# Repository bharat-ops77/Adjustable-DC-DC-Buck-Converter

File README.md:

# Adjustable CC/CV Buck Converter

An open-source, high-efficiency DC-DC step-down buck converter schematic designed in KiCad. It features **Constant Voltage (CV)** and **Constant Current (CC)** control, making it ideal for battery charging, LED driving, and benchtop power supply projects.

---

## ⚡ Key Features

* **Core IC:** XL4015 Step-Down DC-DC Converter (180 kHz PWM).
* **Control Modes:**
  * **Constant Voltage (CV):** Precision output voltage regulation using `RV2`.
  * **Constant Current (CC):** Adjustable current limit control using `RV1`.
* **Precision Voltage Reference:** Built-in `L78L05` + `TL431` voltage reference circuit for stable current limit thresholds.
* **Low-side Current Sensing:** Precision $0.05\ \Omega$ sense resistor monitored via an `LM358` dual op-amp.
* **Status Indicators:** Integrated onboard LEDs for CC/CV active state indication.
* **Protection:** Screw terminal connectors and input fuse protection.
* **Wattage:**  75W with heatsinks and airflow.
---

## Working Principle

### 1. Main Switching Regulator Stage XL4015 (U2): 
A 180 kHz fixed-frequency step-down PWM DC/DC converter capable of driving up to a 5A load.
  #### ● L1 (40uH) & D1 (Schottky Diode): 
  Standard buck topology output LC filtering network and freewheeling diode.
  #### ● C2, C5, C6: 
  Input and output bulk decoupling capacitors to smooth out ripple voltage.
  ### 2. Voltage Regulation (CV Mode)
  The FB (Feedback, Pin 2) pin of the XL4015 expects a reference voltage (typically around 1.25 V).
  #### ● RV2 (10k) & R4/R5:
  RV2 acts as a feedback potentiometer tied to the output line, allowing you to manually adjust and set the target output voltage.
### 3. Current Control & Sensing Stage (CC Mode)
  #### ● Current Sense Resistor (R6 - 0.05ohm): 
  Connected in series with the low-side return ground, generating a small proportional voltage drop based on load current (Vsense = Iout X   0.05ohm).
  ### 4. Precision Reference (U1, U3, RV1):
   #### ● U1 (L78L05): 
   Standard linear regulator generating a clean 5V rail.
   #### ● U3 (TL431): 
   Precision adjustable reference IC producing a ultra-stable voltage.
   #### ● RV1 (10k Potentiometer): 
   Sets the current limit reference threshold for the operational amplifier.
   ### ● Op-Amp Control (U4 - LM358): 
   #### ● U4A : 
   Compares current sense voltage against current reference set by RV1. When current exceeds the threshold, U4A pulls down the feedback pin via D2, forcing the XL4015 to dial back output duty cycle (Constant Current limiting mode).
   #### ● U4B:
   Drives indicator LEDs (D3 / D4) to visually indicate status (e.g., Constant Voltage mode vs. Constant Current/Charging mode).

 ## ● Here is a well labeled diagram of the circuit schematic:

## ● PCB(First Copper Layer):

## ● PCB(Second Copper Layer):

## ● Rendered 3D Model(Angled View):

## ● Rendered 3D Model(Top View):

## ● Rendered PCB(Front):

## ● Rendered PCB(Back):

### ● Repository Structure

```
├── docs/                   # Datasheet of ICs used
├── manufacturing/          # Gerbers & BOM
│   ├── gerbers/            # Gerber and drill files for PCB fabrication
│   ├── bom/                # Bill of Materials (.csv )
├── Adjustable_Buck.kicad_pcb  # KiCad PCB Layout file
├── Adjustable_Buck.kicad_sch  # KiCad Schematic file
├── Adjustable_Buck.kicad_pro  # KiCad Project file
└── README.md               # This file
 #Adjustable CC/CV buck converter
```

### ● Authored by:

#### ---------------------------------------------------------Bharat Sati-------------------------------------------------------------

### ● License:

#### This project is open-source. Feel free to modify, distribute, and use it for your own applications under the GNU License.

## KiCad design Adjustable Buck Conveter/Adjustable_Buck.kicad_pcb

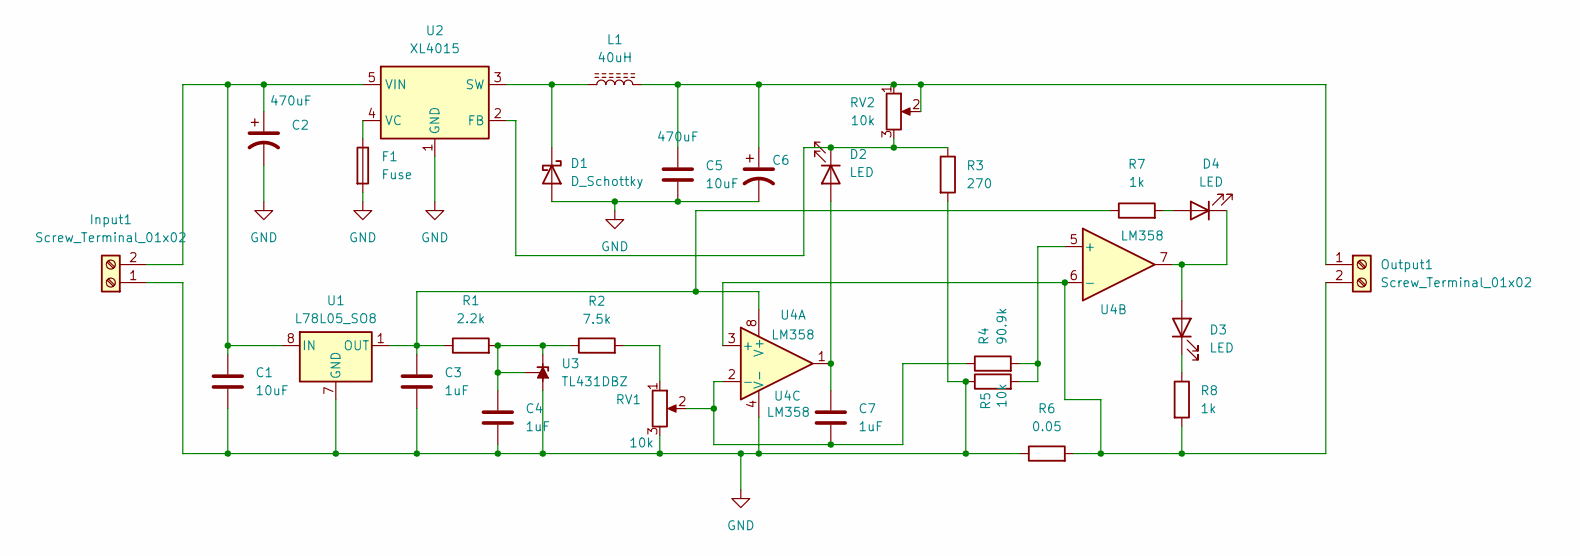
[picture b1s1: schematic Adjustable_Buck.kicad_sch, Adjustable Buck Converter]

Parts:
C1, C5: 10uF; C_Elec_3x5.4
C2, C6: 470uF; CP_Radial_D12.5mm_P7.50mm
C3, C4, C7: 1uF; C_1825_4564Metric_Pad1.57x6.80mm_HandSolder
D1: D_Schottky; D_DO-35_SOD27_P7.62mm_Horizontal
D2, D3, D4: LED; LED_0805_2012Metric
F1: Fuse; Fuse_0603_1608Metric
Input1: Screw_Terminal_01x02; TerminalBlock_MaiXu_MX126-5.0-02P_1x02_P5.00mm
L1: 40uH; L_Radial_D27.9mm_P20.07mm_Vishay_IHB-3
Output1: Screw_Terminal_01x02; TerminalBlock_MaiXu_MX126-5.0-02P_1x02_P5.00mm
R1: 2.2k; R_Axial_DIN0309_L9.0mm_D3.2mm_P12.70mm_Horizontal
R2: 7.5k; R_Axial_DIN0309_L9.0mm_D3.2mm_P12.70mm_Horizontal
R3: 270; R_Axial_DIN0411_L9.9mm_D3.6mm_P12.70mm_Horizontal
R4: 90.9k; R_Axial_DIN0411_L9.9mm_D3.6mm_P12.70mm_Horizontal
R5: 10k; R_Axial_DIN0204_L3.6mm_D1.6mm_P7.62mm_Horizontal
R6: 0.05; R_0201_0603Metric_Pad0.64x0.40mm_HandSolder
R7, R8: 1k; R_Axial_DIN0204_L3.6mm_D1.6mm_P5.08mm_Horizontal
RV1, RV2: 10k; Potentiometer_Bourns_3266Y_Vertical
U1: L78L05_SO8; SOIC-8_3.9x4.9mm_P1.27mm
U2: XL4015; TO-263-5_TabPin3
U3: TL431DBZ; SOT-23
U4: LM358; DIP8_300

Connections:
GND: C1.2, C2.2, C3.2, C4.2, C5.2, C6.2, D1.2 (A), F1.2, Input1.1, R3.2, R5.1, R6.1, RV1.3, U1.2 (GND), U1.3 (GND), U1.6 (GND), U1.7 (GND), U2.1 (GND), U3.3 (A), U4.4 (V-)
unnamed: D1.1 (K), L1.1, U2.3 (SW)
unnamed: C7.1, D2.2 (A), U4.1
unnamed: D2.1 (K), R3.1, RV2.3, U2.2 (FB)
unnamed: D3.2 (A), D4.1 (K), U4.7
unnamed: D3.1 (K), R8.1
unnamed: D4.2 (A), R7.2
unnamed: C1.1, C2.1, Input1.2, U1.8 (IN), U2.5 (VIN)
unnamed: C5.1, C6.1, L1.2, Output1.1, RV2.1, RV2.2
unnamed: Output1.2, R6.2, R8.2, U4.3 (+), U4.6 (-)
unnamed: R2.2, RV1.1
unnamed: C3.1, R1.1, R7.1, U1.1 (OUT), U4.8 (V+)
unnamed: F1.1, U2.4 (VC)
unnamed: C4.1, R1.2, R2.1, U3.1 (K), U3.2 (REF)
unnamed: C7.2, R4.1, RV1.2, U4.2 (-)
unnamed: R4.2, R5.2, U4.5 (+)

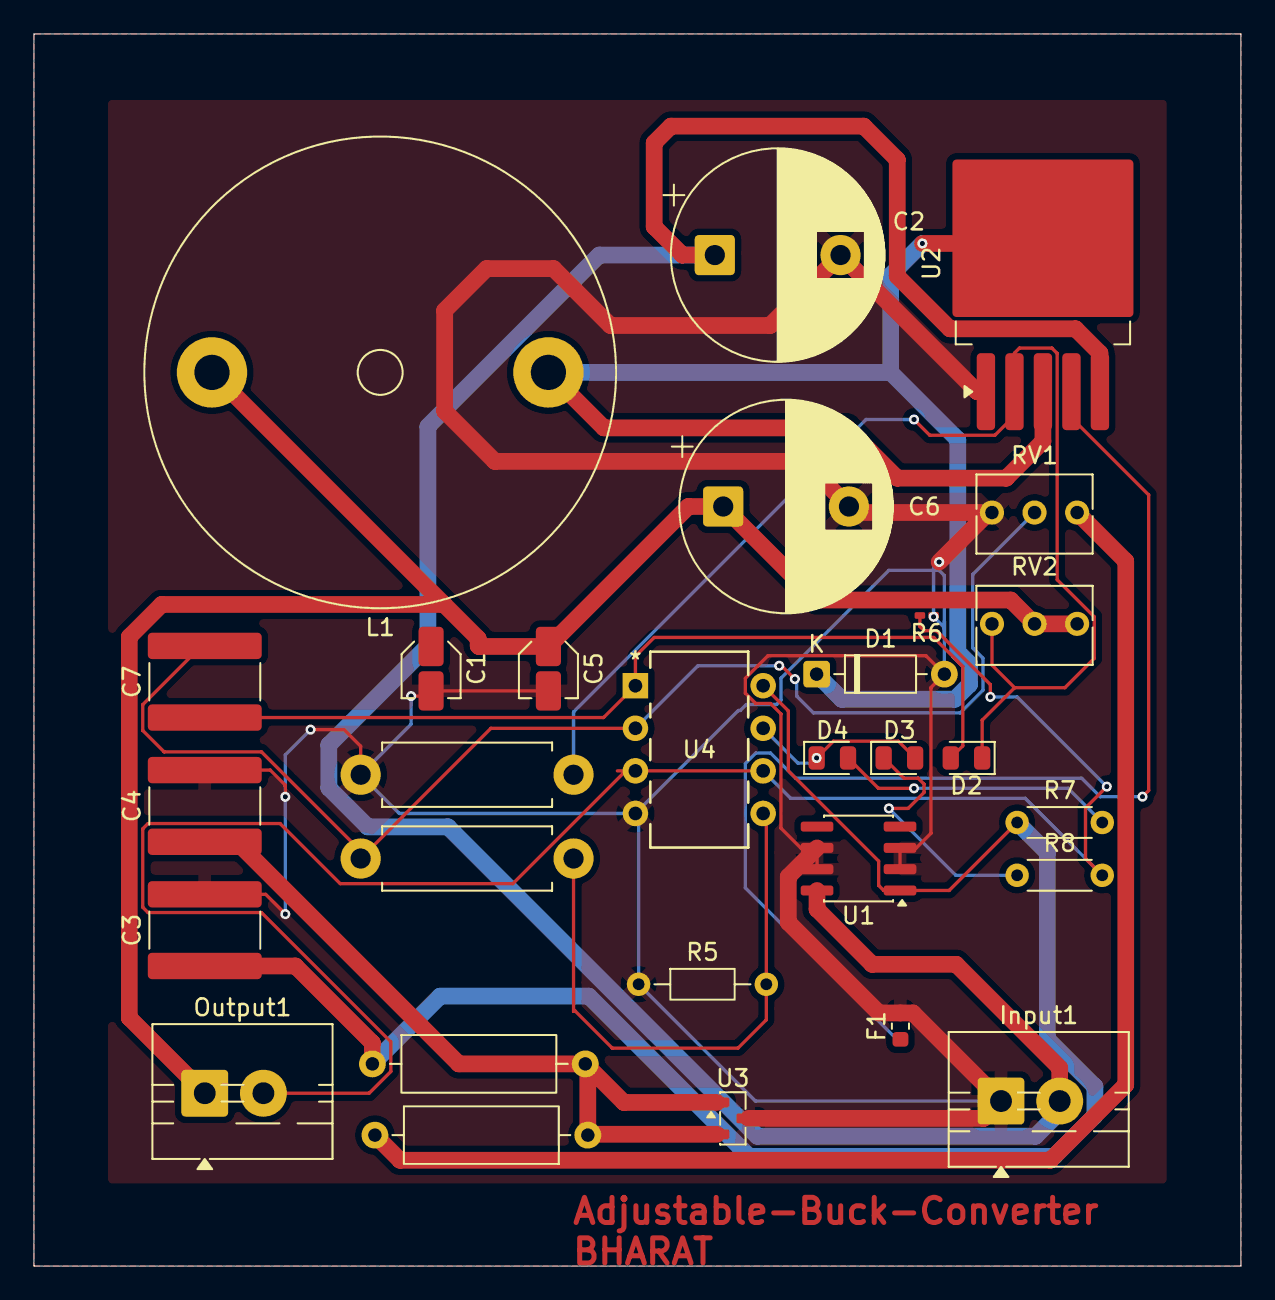
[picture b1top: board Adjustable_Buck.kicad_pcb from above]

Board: 2 copper layers, 72.0 x 73.5 mm, 29 parts (0 on the bottom side), 16 nets.
